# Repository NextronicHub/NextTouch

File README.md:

# Nextronic NextTouch

The NextTouch is a microcontroller board based on the ATmega32u4. It has 20 digital input/output pins (of which 7 can be used as PWM outputs and 12 as analog inputs), a 16 MHz crystal oscillator, a micro USB connection, and a ICSP header. It contains everything needed to support the microcontroller; simply connect it to a computer with a USB cable and get started. 

the ATmega32u4 has built-in USB communication, eliminating the need for a secondary processor. This allows the NextTouch to appear to a connected computer as a mouse and keyboard, in addition to a virtual (CDC) serial / COM port. It also has other implications for the behavior of the board.

Using the NextTouch you can make anything into a key just by connecting a few alligator clips. This allows you to hook up all kinds of fun things as an input.
The NextTouch uses high resistance switching to detect when you've made a connection even through materials that aren't very conductive (like leaves, pasta or people).

## Features

  ATmega32U4 microcontroller w<br />
  Input voltage 5V<br />
  0-5V outputs<br />
  18 Digital capacitive inputs Pins <br />
  6 Analog Inputs<br />
  I2C, UART and SPI<br />
  32k Flash Memory<br />
  16MHz Clock Speed<br />

<br />
<br />

Nextronic Product page:[NextTouch](http://nextronic.ma/product/nextTouch/).

you can by it at: [makershop.ma](http://makershop.ma/).

## Repository Contents

/Hardware - Design files (.brd, .sch)  
/Firmware - bootloader  
/Documentation - datasheet and examples

## Product Versions

NextTouch_V1 first release

## License Information

The hardware is released under [Creative Commons ShareAlike 4.0 International](https://creativecommons.org/licenses/by-sa/4.0/).

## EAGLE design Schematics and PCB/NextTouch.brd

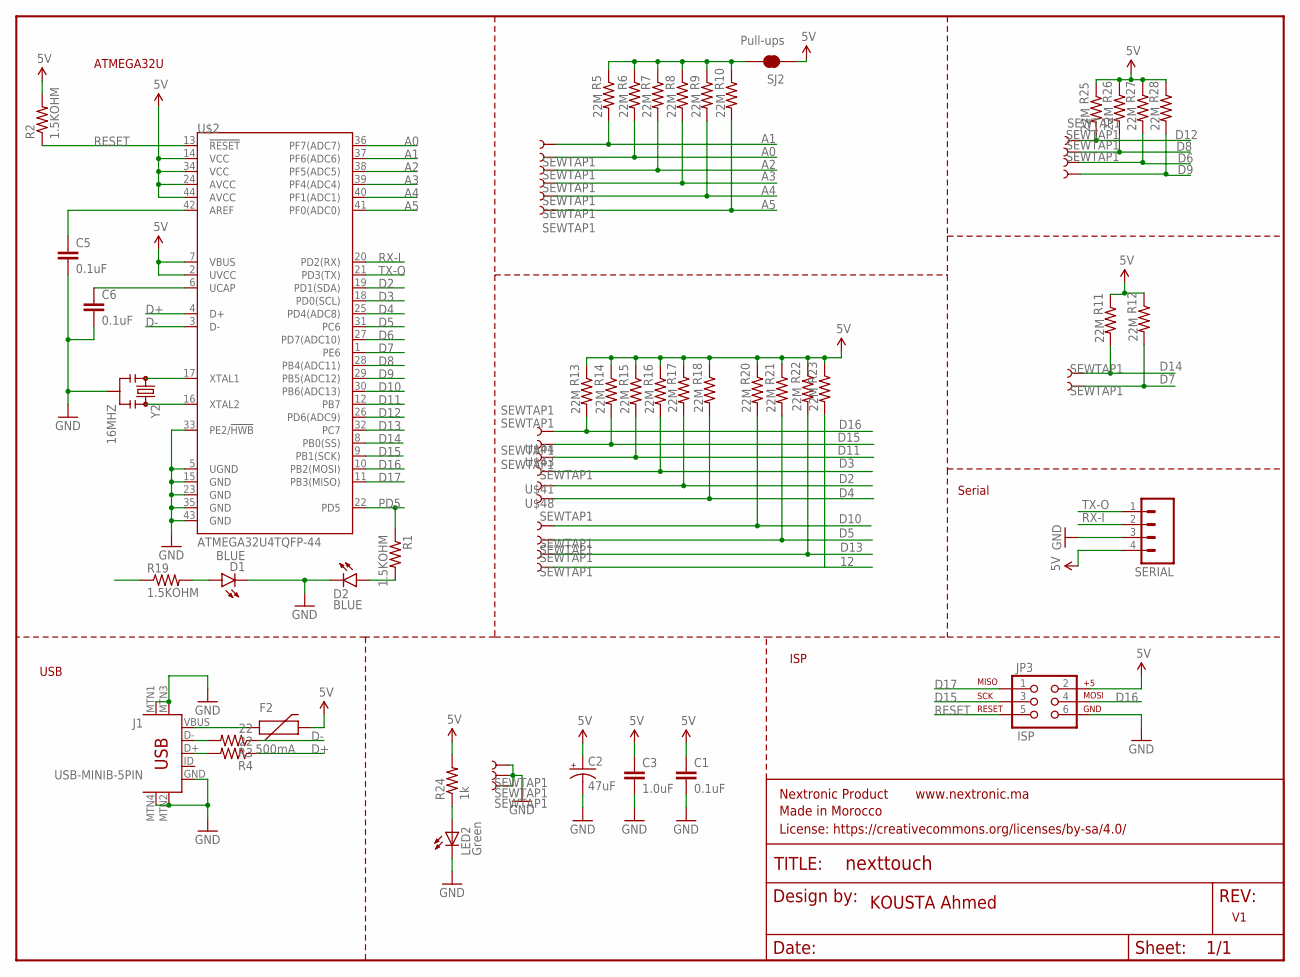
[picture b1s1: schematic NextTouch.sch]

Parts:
C1, C5, C6: 0.1uF; 0603
C2: 47uF; EIA3528
C3: 1.0uF; 0603
D1, D2: BLUE; LED-1206
F2: 500mA; PTC-1206
FRAME1: FRAME-LETTER; CREATIVE_COMMONS
GND: SEWTAP1; PETAL-LONG-1
J1: USB-MINIB-5PIN; USB-MINIB
JP3: ISP; 2X3-NS
LED2: Green; LED-1206-NO_SILK
R1, R2, R19: 1.5KOHM; 0603
R3, R4: 22; 0603
R5, R6, R7, R8, R9, R10, R11, R12, R13, R14, R15, R16, R17, R18, R20, R21, R22, R23, R25, R26, R27, R28: 22M; 0603
R24: 1k; 0603-RES
SERIAL: M04PTH; 1X04
SJ2: Pull-ups; SJ_2S-TRACE
U$2: ATMEGA32U4TQFP-44; TQFP44
U$3, U$4, U$5, U$6, U$7, U$30, U$31, U$32, U$33, U$34, U$35, U$36, U$37, U$38, U$39, U$40, U$41, U$42, U$43, U$44, U$45, U$46, U$48, U$51: SEWTAP1; PETAL-LONG-1
Y2: 16MHZ; RESONATOR-SMD

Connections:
5V: C1.1, C2.A (+), C3.1, F2.2, JP3.2, R2.2, R11.1, R12.1, R13.1, R14.1, R15.1, R16.1, R17.1, R18.1, R20.1, R21.1, R22.1, R23.1, R24.2, R25.1, R26.1, R27.1, R28.1, SERIAL.4, SJ2.1, U$2.2 (UVCC), U$2.7 (VBUS), U$2.14 (VCC), U$2.24 (AVCC), U$2.34 (VCC), U$2.44 (AVCC)
12: R23.2, U$51.1
A0: R6.2, U$2.36 (PF7(ADC7)), U$40.1
A1: R5.2, U$2.37 (PF6(ADC6)), U$4.1
A2: R7.2, U$2.38 (PF5(ADC5)), U$31.1
A3: R8.2, U$2.39 (PF4(ADC4)), U$32.1
A4: R9.2, U$2.40 (PF1(ADC1)), U$33.1
A5: R10.2, U$2.41 (PF0(ADC0)), U$34.1
D2: R17.2, U$2.19 (PD1(SDA)), U$48.1
D3: R16.2, U$2.18 (PD0(SCL)), U$41.1
D4: R18.2, U$2.25 (PD4(ADC8)), U$35.1
D5: R21.2, U$2.31 (PC6), U$38.1
D6: R27.2, U$2.27 (PD7(ADC10)), U$7.1
D7: R12.2, U$2.1 (PE6), U$46.1
D8: R26.2, U$2.28 (PB4(ADC11)), U$6.1
D9: R28.2, U$2.29 (PB5(ADC12)), U$3.1
D10: R20.2, U$2.30 (PB6(ADC13)), U$37.1
D11: R15.2, U$2.12 (PB7), U$42.1
D12: R25.2, U$2.26 (PD6(ADC9)), U$5.1
D13: R22.2, U$2.32 (PC7), U$39.1
D14: R11.2, U$2.8 (PB0(SS)), U$45.1
D15: JP3.3, R14.2, U$2.9 (PB1(SCK)), U$43.1
D16: JP3.4, R13.2, U$2.10 (PB2(MOSI)), U$44.1
D17: JP3.1, R19.1, U$2.11 (PB3(MISO))
D+: R4.1, U$2.4 (D+)
D-: R3.1, U$2.3 (D-)
GND: C1.2, C2.C (-), C3.2, C5.2, C6.2, D1.C, D2.C, GND.1, J1.GND, J1.MTN1 (MTN2), J1.MTN2 (MTN3), J1.MTN3 (MTN1), J1.MTN4, JP3.6, LED2.C, SERIAL.3, U$2.5 (UGND), U$2.15 (GND), U$2.23 (GND), U$2.33 (PE2/!HWB), U$2.35 (GND), U$2.43 (GND), U$30.1, U$36.1, Y2.2
unnamed: D2.A, R1.2
unnamed: LED2.A, R24.1
unnamed: D1.A, R19.2
unnamed: U$2.17 (XTAL1), Y2.1
unnamed: U$2.16 (XTAL2), Y2.3
unnamed: C5.1, U$2.42 (AREF)
unnamed: R5.1, R6.1, R7.1, R8.1, R9.1, R10.1, SJ2.2
unnamed: F2.1, J1.VBUS
unnamed: C6.1, U$2.6 (UCAP)
unnamed: J1.D-, R3.2
unnamed: J1.D+, R4.2
PD5: R1.1, U$2.22 (PD5)
RESET: JP3.5, R2.1, U$2.13 (!RESET)
RX-I: SERIAL.2, U$2.20 (PD2(RX))
TX-O: SERIAL.1, U$2.21 (PD3(TX))

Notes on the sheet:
ATMEGA32U
USB
KOUSTA Ahmed
ISP
Serial

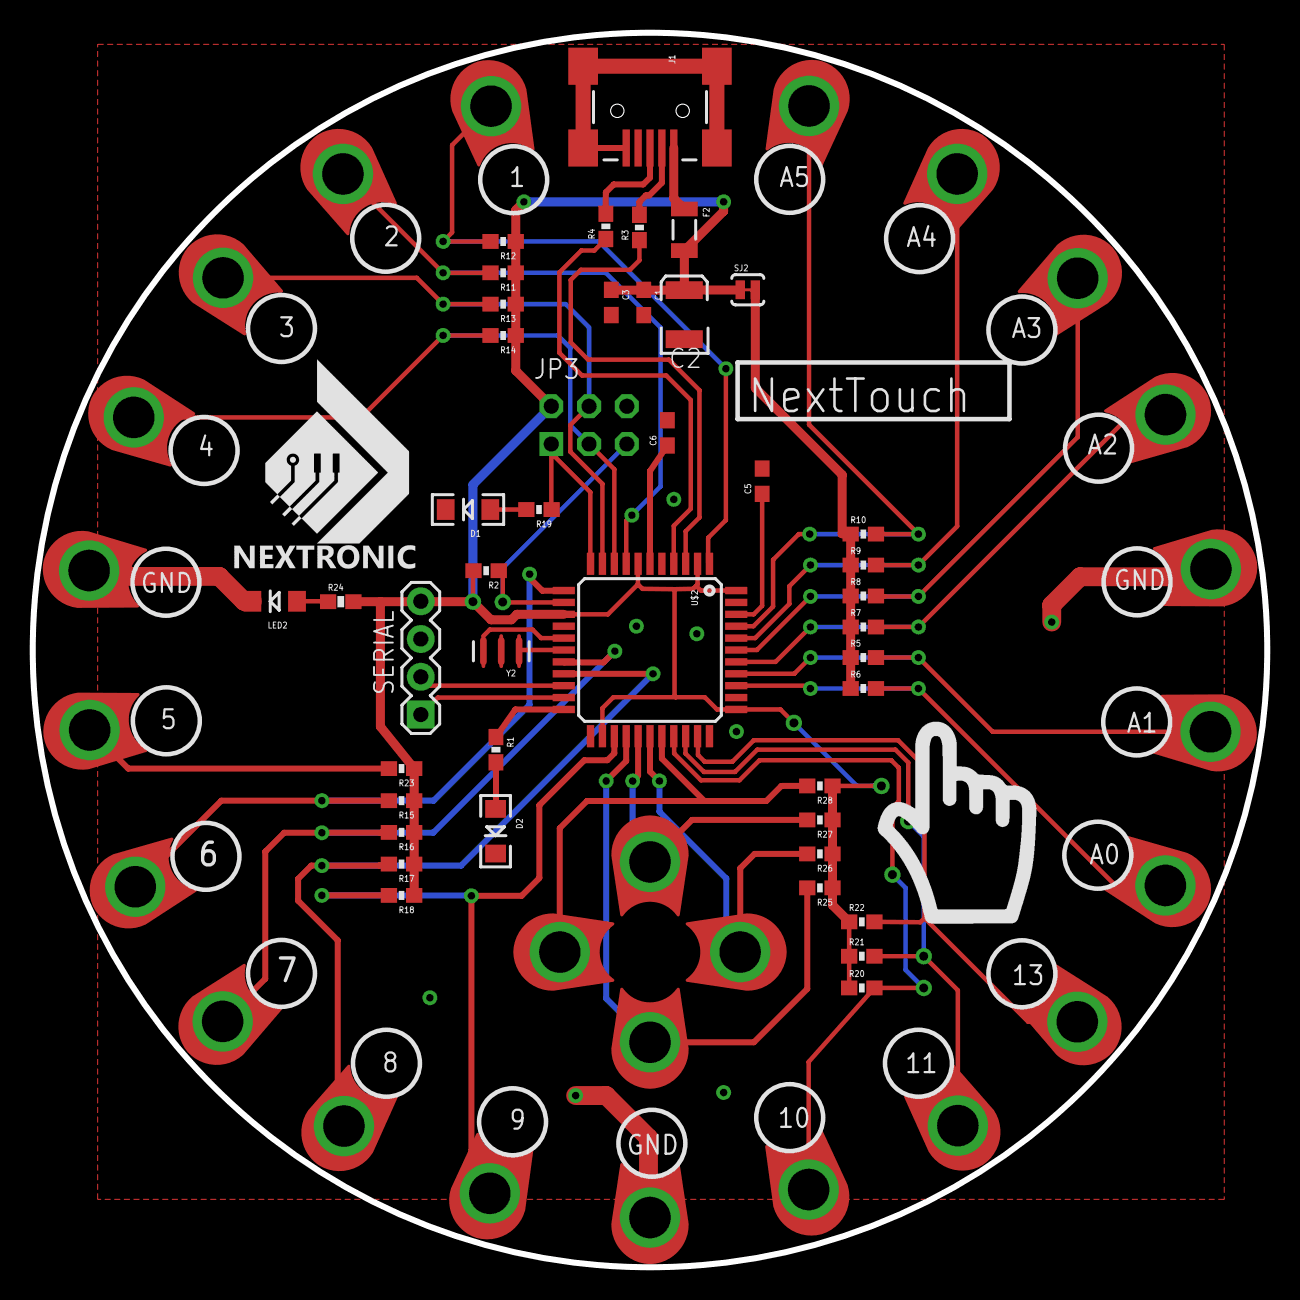
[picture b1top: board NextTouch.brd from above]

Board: 2 copper layers, 83.0 x 83.0 mm, 69 parts (0 on the bottom side), 42 nets.

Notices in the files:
parts and their libraries:
SparkFun-DigitalIC: Licensing: Creative Commons ShareAlike 4.0 International - https://creativecommons.org/licenses/by-sa/4.0
SparkFun-LED: Licensing: CC v3.0 Share-Alike You are welcome to use this library for commercial purposes.
